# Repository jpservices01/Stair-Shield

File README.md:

# Stair-Shield
Project to control the LEDs in a staircase using a Arduino Mega 2560 and the shield uploaded here
The idea is to use a shift register to control the Leds independently so that there is not too much power drawn to the Mega 2560 controller. The shift register output intensity is controlled by one resistor and a PWM output.

There are actually one control per stairs with 15 Leds per stairs.

Used Kicad version 4.0.1
Used PCBNew 4.0.1

On PCB version 1.0
Had initially vias set to 0.6 mm with a drill of 0.4mm. PCB Tools said that rest material should be at least 0.15mm and therefore increased vias to 0.7mm with the same drill.

PCB Version 1.1
Corrected the above and remove vias from texts. Also changed the design rules to have at least vias of 0.7mm

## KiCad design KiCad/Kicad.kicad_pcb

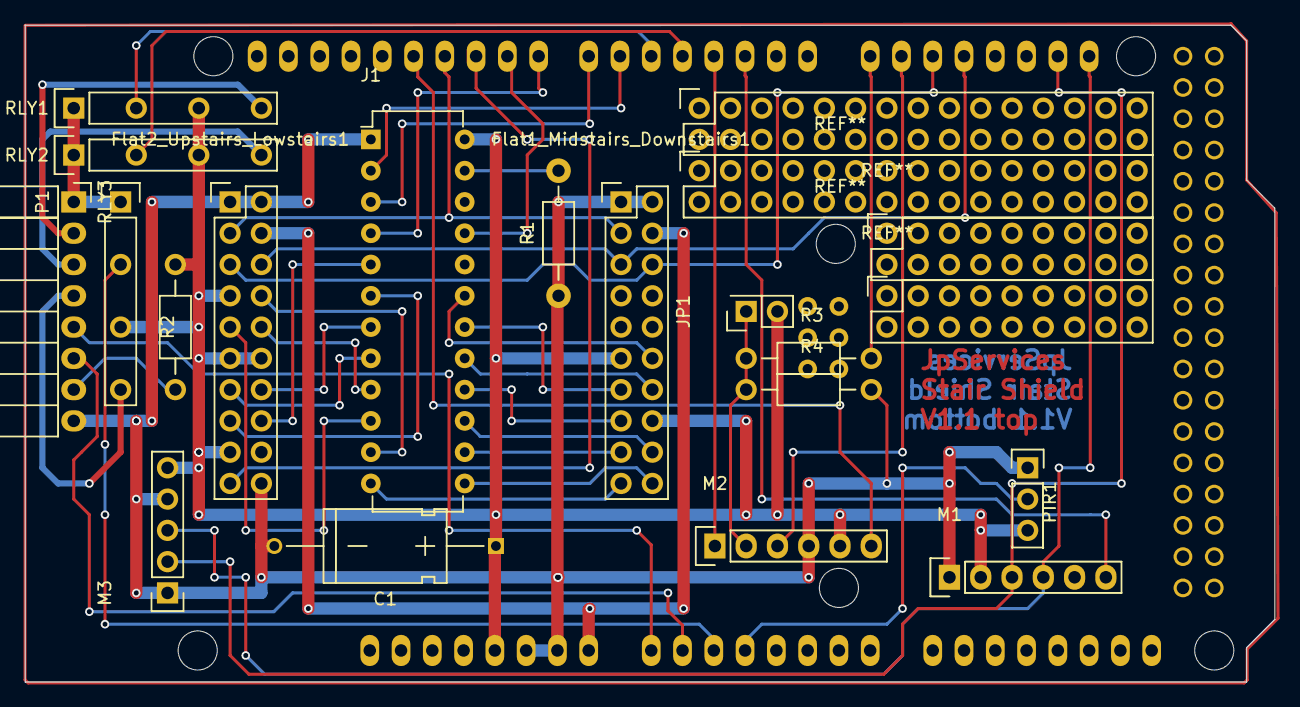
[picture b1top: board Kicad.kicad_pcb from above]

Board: 2 copper layers, 101.5 x 53.3 mm, 18 parts (0 on the bottom side), 46 nets.

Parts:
C1: CP1; C_Axial_D6_L11_P18
Flat1_Midstairs_Downstairs1, Flat2_Upstairs_Lowstairs1: CONN_02X10; Pin_Header_Straight_2x10
J1: DM13A; DIP-24_W7.62mm
JP1: JUMPER; Socket_Strip_Straight_2x01
LED_Master_2nd_Floor1: ARDUINO_MEGA_SHIELD
M1: RTC3231
M2: HC-05; HC05
M3: BH1750FVI
P1: CONN_01X08; Socket_Strip_Angled_1x08
PIR1: PIR_Motion_Sensor; HC-SR505
R1: 270; Resistor_Horizontal_RM10mm
R2: R; Resistor_Horizontal_RM10mm
R3: 1K; Resistor_Horizontal_RM10mm
R4: 2K; Resistor_Horizontal_RM10mm
RLY1, RLY2, RLY3: RELAY_SIP_1A05; Socket_Strip_Straight_1x07_5.08

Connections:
+5V: C1.1, Flat1_Midstairs_Downstairs1.11, Flat1_Midstairs_Downstairs1.16, Flat2_Upstairs_Lowstairs1.7, Flat2_Upstairs_Lowstairs1.11, Flat2_Upstairs_Lowstairs1.12, Flat2_Upstairs_Lowstairs1.17, J1.24, JP1.2, LED_Master_2nd_Floor1.5V, M1.2, M2.5, M3.5, PIR1.3, R2.1, RLY1.5, RLY2.5, RLY3.5
/Bell Control/BellDownOn: LED_Master_2nd_Floor1.5, RLY1.3
/Bell Control/BellUpOn: LED_Master_2nd_Floor1.4, RLY2.3
/Bell Control/DoorStrikeOn: LED_Master_2nd_Floor1.AD2, RLY3.3
/Bell Control/RingDown: LED_Master_2nd_Floor1.AD0, P1.5
/Bell Control/RingUp: LED_Master_2nd_Floor1.AD1, P1.6
GND: C1.2, Flat1_Midstairs_Downstairs1.1, Flat1_Midstairs_Downstairs1.2, Flat2_Upstairs_Lowstairs1.1, Flat2_Upstairs_Lowstairs1.2, Flat2_Upstairs_Lowstairs1.20, J1.1, LED_Master_2nd_Floor1.GND1, LED_Master_2nd_Floor1.GND2, M1.1, M2.4, M3.1, M3.4, P1.8, PIR1.1, R1.1, R4.2
unnamed: Flat1_Midstairs_Downstairs1.3, Flat2_Upstairs_Lowstairs1.3, LED_Master_2nd_Floor1.11
unnamed: Flat1_Midstairs_Downstairs1.4, Flat2_Upstairs_Lowstairs1.4, LED_Master_2nd_Floor1.V_IN
unnamed: Flat1_Midstairs_Downstairs1.5, Flat2_Upstairs_Lowstairs1.6, LED_Master_2nd_Floor1.17
unnamed: Flat1_Midstairs_Downstairs1.6, Flat2_Upstairs_Lowstairs1.5, LED_Master_2nd_Floor1.16
unnamed: Flat1_Midstairs_Downstairs1.12, J1.19
unnamed: Flat1_Midstairs_Downstairs1.13, J1.18
unnamed: Flat1_Midstairs_Downstairs1.14, J1.17
unnamed: Flat1_Midstairs_Downstairs1.15, J1.16
unnamed: Flat1_Midstairs_Downstairs1.17, J1.14
unnamed: Flat1_Midstairs_Downstairs1.18, J1.15
unnamed: Flat1_Midstairs_Downstairs1.19, J1.12
unnamed: Flat1_Midstairs_Downstairs1.20, J1.13
unnamed: Flat2_Upstairs_Lowstairs1.8, J1.11
unnamed: Flat2_Upstairs_Lowstairs1.9, J1.10
unnamed: Flat2_Upstairs_Lowstairs1.10, J1.9
unnamed: Flat2_Upstairs_Lowstairs1.13, J1.8
unnamed: Flat2_Upstairs_Lowstairs1.14, J1.7
unnamed: Flat2_Upstairs_Lowstairs1.15, J1.6
unnamed: Flat2_Upstairs_Lowstairs1.16, J1.5
unnamed: Flat2_Upstairs_Lowstairs1.19, LED_Master_2nd_Floor1.10
unnamed: J1.2, LED_Master_2nd_Floor1.6
unnamed: J1.3, LED_Master_2nd_Floor1.7
unnamed: J1.4, LED_Master_2nd_Floor1.8
unnamed: J1.21, LED_Master_2nd_Floor1.9
unnamed: J1.23, R1.2
unnamed: JP1.1, M2.2, R3.1, R4.1
unnamed: LED_Master_2nd_Floor1.2, M1.6
unnamed: LED_Master_2nd_Floor1.3, M2.1
unnamed: LED_Master_2nd_Floor1.12, M2.6
unnamed: LED_Master_2nd_Floor1.14, R3.2
unnamed: LED_Master_2nd_Floor1.15, M2.3
unnamed: LED_Master_2nd_Floor1.20, M1.3, M3.2
unnamed: LED_Master_2nd_Floor1.21, M1.4, M3.3
unnamed: LED_Master_2nd_Floor1.AD3, PIR1.2
unnamed: P1.1, RLY1.1, RLY2.1, RLY3.1
unnamed: P1.2, RLY1.7
unnamed: P1.3, RLY2.7
unnamed: P1.4, RLY3.7
unnamed: P1.7, R2.2

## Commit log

2016-06-08 Create README.txt
    Arduino files
2016-06-08 Add files via upload
    Kicad master file
2016-06-08 Add files via upload
    Kicad PCBnew PCB file
2016-06-08 Add files via upload
    Schematic of the Arduino shield
2016-06-08 Create README.txt
    bell interface schematic
2016-06-08 Add files via upload
    Master kicad file
2016-06-08 Add files via upload
    Schematic
2016-06-08 Add files via upload
    Control software for Arduino for the first floor and the stair shield
